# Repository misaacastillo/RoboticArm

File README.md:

# ROBOTIC ARM

“Robotic Arm” es un brazo robotico el cual cuenta con un modelo dummy de menores dimensiones.
Este modelo copia tendrá una conexión entre sus potenciómetros y los servomotores ubicados en el modelo principal.
Al mover con la mano las 4 articulaciones del modelo dummy provocará que el modelo original se mueva por su cuenta y en sincronía. 
Además el modelo dummy contará con un botón en el extremo superior del brazo, el cual al ser presionado, accionará la pinza ubicada en el extremo superior del modelo original. 

## BRAZO PRINCIPAL:

## MODELO DUMMY:

## Contacto
### Misael Castillo
* 📷 Instagram: [@misaacas](https://www.instagram.com/misaacas/)
* 📧 Mail: misacastillo08@gmail.com
* 🏆 LinkedIn: [Castillo Misael](https://www.linkedin.com/in/misael-castillo-0a52a1314/)
* 🌐 Github: [misaacastillo](https://github.com/misaacastillo)

## 📜 Licencia

Este proyecto está licenciado bajo la [MIT License](LICENSE).  
© 2024 Robotic Arm By Misael Castilo

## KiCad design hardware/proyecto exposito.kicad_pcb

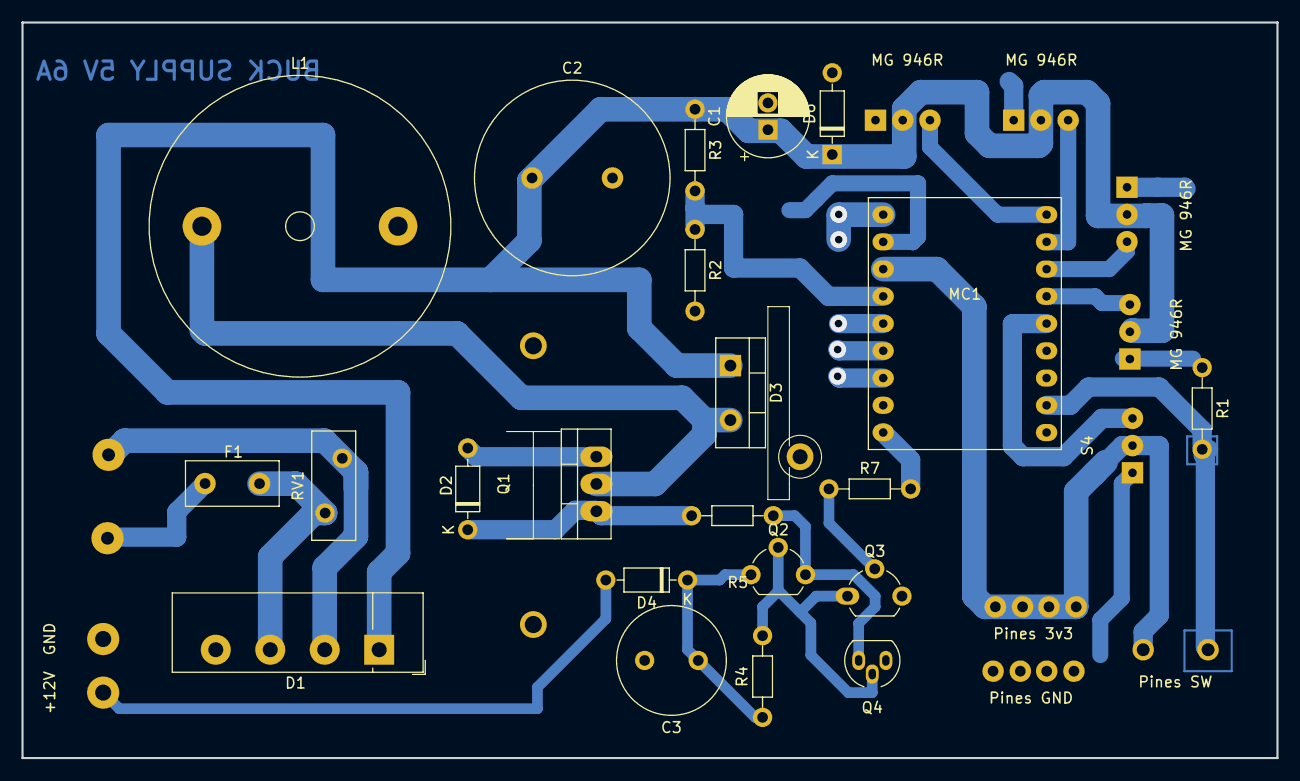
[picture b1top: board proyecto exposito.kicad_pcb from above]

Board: 2 copper layers, 117.1 x 68.6 mm, 30 parts (0 on the bottom side), 19 nets.

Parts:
C1: C; CP_Radial_D7.5mm_P2.50mm
C2: C; C_Radial_D18.0mm_H35.5mm_P7.50mm
C3: C; C_Radial_D10.0mm_H20.0mm_P5.00mm
D1: KBU6M; Diode_Bridge_Vishay_KBU
D2, D6: D_Zener; D_DO-35_SOD27_P7.62mm_Horizontal
D3: MBR745; TO-220-2_Vertical
D4: 1N4007; D_DO-35_SOD27_P7.62mm_Horizontal
F1: Fuse; Fuse_Littelfuse_395Series
L1: L; L_Radial_D27.9mm_P18.29mm_Vishay_IHB-3
MC1: RP2040-Zero
Pines 3v3: Terminal; TerminalBlock_Xinya_XY308-2.54-3P_1x03_P2.54mm_Horizontal
Pines GND: Terminal; TerminalBlock_Xinya_XY308-2.54-3P_1x03_P2.54mm_Horizontal
Q1: IRF840N; TO-220-3_Vertical
Q2, Q3: BC548; TO-92_Wide
Q4: BC558; TO-92_HandSolder
R1: R Pull Down; R_Axial_DIN0204_L3.6mm_D1.6mm_P7.62mm_Horizontal
R2, R3: R; R_Axial_DIN0204_L3.6mm_D1.6mm_P7.62mm_Horizontal
R4: 470; R_Axial_DIN0204_L3.6mm_D1.6mm_P7.62mm_Horizontal
R5: 47; R_Axial_DIN0204_L3.6mm_D1.6mm_P7.62mm_Horizontal
R7: 4k7; R_Axial_DIN0204_L3.6mm_D1.6mm_P7.62mm_Horizontal
RV1: Varistor; Fuse_BelFuse_0ZRE0016FF_L9.9mm_W3.8mm
S0: Terminal; TerminalBlock_Xinya_XY308-2.54-3P_1x03_P2.54mm_Horizontal
S1, S2, S3: terminal; TerminalBlock_Xinya_XY308-2.54-3P_1x03_P2.54mm_Horizontal
S4: SG90; TerminalBlock_Xinya_XY308-2.54-3P_1x03_P2.54mm_Horizontal
pines: Terminal; TerminalBlock_Xinya_XY308-2.54-3P_1x03_P2.54mm_Horizontal

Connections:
+3V3: MC1.21 (3V3), Pines 3v3.1, pines.1
GND: C1.2, C2.2, C3.2, D1.4 (-), D2.2 (A), D6.2 (A), L1.2, MC1.23 (GND), Pines GND.1, Q1.3 (S), Q3.3 (E), Q4.1 (C), R1.1, R2.2, S0.1, S1.1, S2.1, S3.1, S4.1
GP0: MC1.1 (GP0), S1.3
GP1: MC1.2 (GP1), S2.3
GP2: MC1.3 (GP2), S3.3
GP3: MC1.4 (GP3), S0.3
GP4: MC1.5 (GP4), S4.3
unnamed: D1.2, RV1.2
unnamed: D1.3, F1.2, RV1.1
unnamed: D3.2 (A), L1.1, Q1.2 (D)
unnamed: C3.1, D4.1 (K), Q2.1 (C), R4.1
unnamed: MC1.8 (GP7), R1.2
unnamed: Q2.2 (B), Q3.1 (C), Q4.2 (B), R4.2
unnamed: Q2.3 (E), Q4.3 (E), R5.1
unnamed: Q3.2 (B), R7.1
PWM: MC1.15 (GP14), R7.2
PWM 12V: D2.1 (K), Q1.1 (G), R5.2
Vout: C1.1, C2.1, D1.1 (+), D3.1 (K), D6.1 (K), R3.1, S0.2, S1.2, S2.2, S3.2
Vref: MC1.20 (GP29), R2.1, R3.2

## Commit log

2024-11-26 Create PCB
2024-11-26 Create PCB & ESQUEMATICO
2024-11-26 Update pcb
2024-11-27 Create Esquematico
2024-11-27 Create src
2024-11-27 Create GG
2024-11-27 Create Controller STL files
2024-11-27 Create h
2025-04-03 docs(readme): se agrega contactos y licencia del proyecto
